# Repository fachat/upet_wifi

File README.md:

# Wifi breakout module for Micro-PET 3.x, Ultra-CPU 2.x, and Ulti-PET 1.x

This is part of a larger project with multiple boards, with [upet_family](https://github.com/fachat/upet_family) as parent repository.

This module implements a Wifi module for the [Micro-PET](https://github.com/fachat/cbm_micropet), the [Ultra-CPU](https://github.com/fachat/csa_ultracpu), and the [Ulti-PET](https://github.com/fachat/cbm_ultipet). These boards provide an SPI-based breakout connector, which this module plugs in to.

The Wifi-Module used is an ESP32-C3-WROOM-02 module that uses two serial (rs232 on 3.3V TTL level) interfaces - one for firmware updates and logs, the other for the AT commands used to control the communication.
To connect to the main board, this breakout board uses a dual-UART SC16IS752 that has an SPI interface to control it.

## Build

This repository contains the KiCad schematics and PCB layout, as well as gerber files (gerbers directory). and the interactive BOM (bom directory).
Also, in the bom directory is a full XLSX format BOM with manufacturer and Mouser and JLCPCB part numbers, that you can upload to your favourite parts provider.

[Schematics PDF](UPET-Wifi-Schematics.pdf)

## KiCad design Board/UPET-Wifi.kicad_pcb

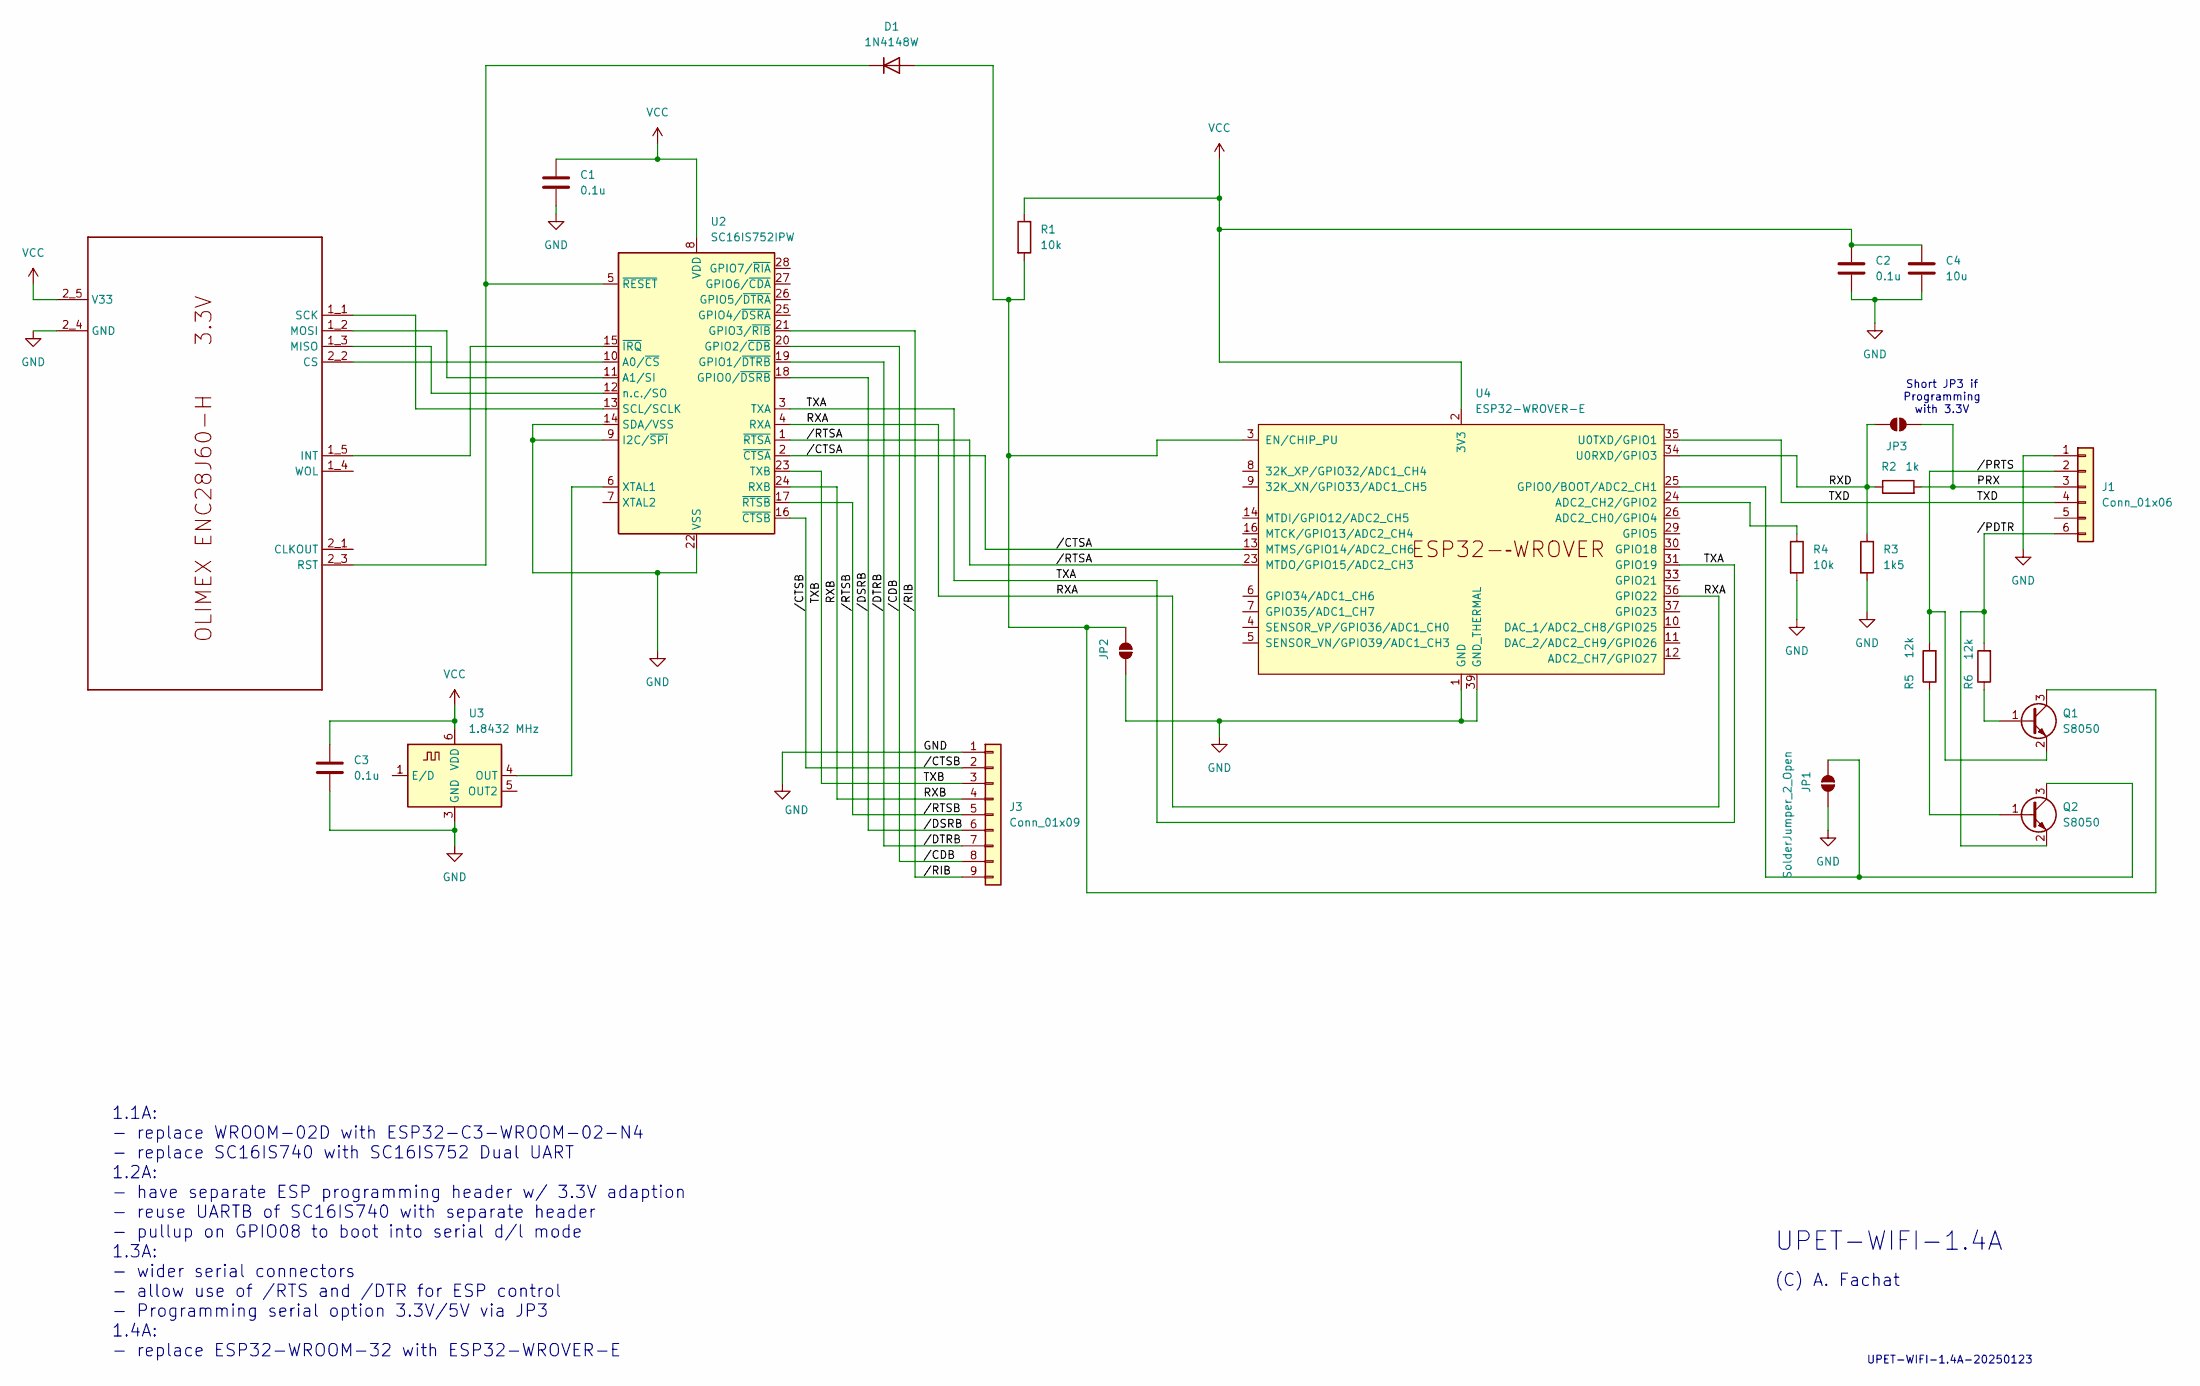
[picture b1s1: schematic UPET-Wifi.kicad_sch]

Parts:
C1, C2, C3: 0.1u; C_0603_1608Metric_Pad1.08x0.95mm_HandSolder
C4: 10u; C_0603_1608Metric_Pad1.08x0.95mm_HandSolder
D1: 1N4148W; D_SOD-123
J1: Conn_01x06; PinHeader_1x06_P2.54mm_Vertical
J3: Conn_01x09; PinHeader_1x09_P2.54mm_Vertical
JP1, JP2, JP3: SolderJumper_2_Open; SolderJumper-2_P1.3mm_Open_RoundedPad1.0x1.5mm
Q1, Q2: S8050; SOT-23
R1, R4: 10k; R_0603_1608Metric_Pad0.98x0.95mm_HandSolder
R2: 1k; R_0603_1608Metric_Pad0.98x0.95mm_HandSolder
R3: 1k5; R_0603_1608Metric_Pad0.98x0.95mm_HandSolder
R5, R6: 12k; R_0603_1608Metric_Pad0.98x0.95mm_HandSolder
U2: SC16IS752IPW; TSSOP-28_4.4x9.7mm_P0.65mm
U3: 1.8432 MHz; Oscillator_SMD_IDT_JU6-6_7.0x5.0mm_P2.54mm
U4: ESP32-WROVER-E
U$1: uPET NET SPI; UPET_NETSPI

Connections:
/PRX: J1.3, JP3.1 (A), R2.2
/RXA: U2.4 (RXA), U4.36 (GPIO22)
/RXB: J3.4, U2.24 (RXB)
/RXD: JP3.2 (B), R2.1, R3.1, U4.34 (U0RXD/GPIO3)
/TXA: U2.3 (TXA), U4.31 (GPIO19)
/TXB: J3.3, U2.23 (TXB)
/TXD: J1.4, U4.35 (U0TXD/GPIO1)
//CDB: J3.8, U2.20 (GPIO2/~CDB)
//CTSA: U2.2 (~CTSA), U4.13 (MTMS/GPIO14/ADC2_CH6)
//CTSB: J3.2, U2.16 (~CTSB)
//DSRB: J3.6, U2.18 (GPIO0/~DSRB)
//DTRB: J3.7, U2.19 (GPIO1/~DTRB)
//PRTS: J1.2, Q1.2 (E), R5.2
//RIB: J3.9, U2.21 (GPIO3/~RIB)
//RTSA: U2.1 (~RTSA), U4.23 (MTDO/GPIO15/ADC2_CH3)
//RTSB: J3.5, U2.17 (~RTSB)
GND: C1.2, C2.2, C3.2, C4.2, J1.1, J3.1, JP1.1 (A), JP2.1 (A), R3.2, R4.2, U2.9 (I2C/~SPI), U2.14 (SDA/VSS), U2.22 (VSS), U3.3 (GND), U4.1 (GND), U4.15 (GND), U4.38 (GND), U4.39 (GND_THERMAL), U$1.2_4 (GND)
unnamed: D1.2 (A), JP2.2 (B), Q1.3 (C), R1.2, U4.3 (EN/CHIP_PU)
unnamed: D1.1 (K), U2.5 (~RESET), U$1.2_3 (RST)
unnamed: J1.6, Q2.2 (E), R6.2
unnamed: JP1.2 (B), Q2.3 (C), U4.25 (GPIO0/BOOT/ADC2_CH1)
unnamed: Q1.1 (B), R6.1
unnamed: Q2.1 (B), R5.1
unnamed: U2.6 (XTAL1), U3.4 (OUT)
unnamed: R4.1, U4.24 (ADC2_CH2/GPIO2)
unnamed: U2.10 (A0/~CS), U$1.2_2 (CS)
unnamed: U2.15 (~IRQ), U$1.1_5 (INT)
unnamed: U2.12 (n.c./SO), U$1.1_3 (MISO)
unnamed: U2.11 (A1/SI), U$1.1_2 (MOSI)
unnamed: U2.13 (SCL/SCLK), U$1.1_1 (SCK)
VCC: C1.1, C2.1, C3.1, C4.1, R1.1, U2.8 (VDD), U3.6 (VDD), U4.2 (3V3), U$1.2_5 (V33)

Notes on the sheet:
(C) A. Fachat
1.1A: - replace WROOM-02D with ESP32-C3-WROOM-02-N4 - replace SC16IS740 with SC16IS752 Dual UART 1.2A: - have separate ESP programming header w/ 3.3V adaption - reuse UARTB of SC16IS740 with separate header - pullup on GPIO08 to boot into serial d/l mode 1.3A: - wider serial connectors - allow use 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
Short JP3 if Programming with 3.3V
UPET-WIFI-1.4A
UPET-WIFI-1.4A-20250123

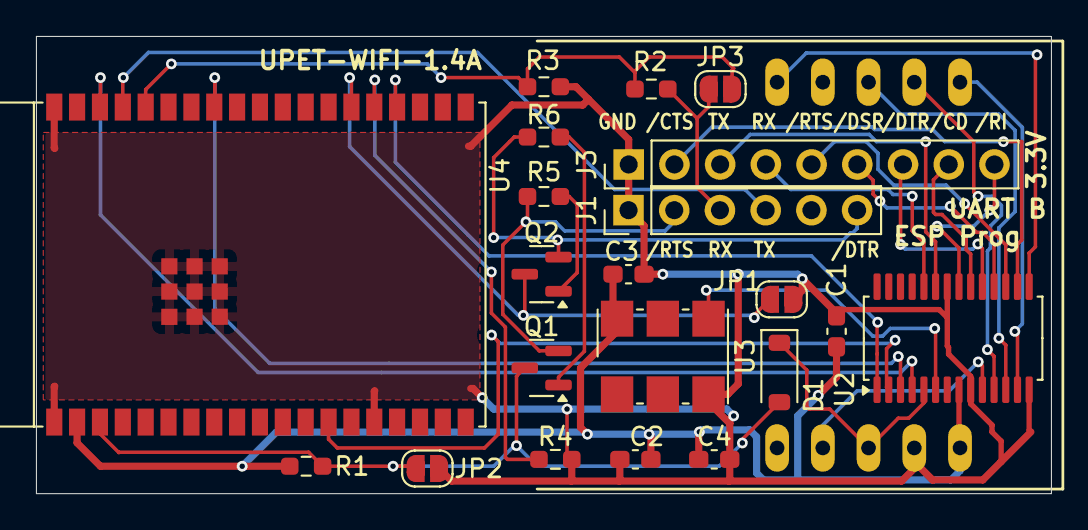
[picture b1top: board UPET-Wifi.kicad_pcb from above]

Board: 2 copper layers, 56.4 x 25.4 mm, 22 parts (0 on the bottom side), 31 nets.

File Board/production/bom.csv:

Designator,Footprint,Quantity,Value,LCSC Part #
"C1, C2, C3",0603,3,0.1u,
C4,0603,1,10u,
D1,D_SOD-123,1,1N4148W,
J1,PinHeader_1x06_P2.54mm_Vertical,1,Conn_01x06,
J3,PinHeader_1x09_P2.54mm_Vertical,1,Conn_01x09,
"Q1, Q2",SOT-23,2,S8050,
"R1, R4",0603,2,10k,
R2,0603,1,1k,
R3,0603,1,1k5,
"R5, R6",0603,2,12k,
U$1,UPET_NETSPI,1,uPET NET SPI,
U2,TSSOP-28_4.4x9.7mm_P0.65mm,1,SC16IS752IPW,
U3,Oscillator_SMD_IDT_JU6-6_7.0x5.0mm_P2.54mm,1,1.8432 MHz,
U4,ESP32-WROVER-E,1,ESP32-WROVER-E,

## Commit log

2024-06-18 initial commit upet-wifi 1.1a
2024-06-20 add link to family repo
2024-06-20 cleanup, move files
2024-06-26 handle (no) sub repos
2024-07-24 start working on skeleton for driver
2024-07-24 first init of UART
2024-07-25 fix divisor setting
2024-07-26 add support for std parallel UART
2024-07-26 add transfer tool between wifi uart and upet uart
2024-07-28 optimizations
2024-07-28 enable auto-rts/cts on seruart
2024-08-03 add sendbrk
2024-09-03 move to 1.2 - separate serial prog interface
2025-01-19 work on wifi 1.3a
2025-01-19 gerbers, bom, etc
2025-01-22 production files
2025-01-22 image
2025-01-22 add links to pdfs
2025-01-22 remove board pdf
2025-01-23 replace ESP32-WROOM with an ESP32-VROVER-E
2025-01-23 update 3d images
2025-01-23 update bom
